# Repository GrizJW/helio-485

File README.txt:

Helio-485 Rev A — KiCad layout

Open helio-485.kicad_pcb. KiCad 10 (file version 20260206).

Board: 140 x 218 mm, 2 layer, 1.6 mm, 2 oz. No cell holders.
J5 is the 2S pouch (PACK−, PACK+). J6 is the balance lead (PACK−, midpoint, PACK+). Charge current is
set to 2 A, which is the TP5100 limit. U10 is an LM393 low-voltage
disconnect: it forces the 12 V boost off below 6.4 V on the pack.
J7 is the Ethernet jack. U11 is a W5500. The C5 has no MAC.

What is already done
- Official KiCad footprints for the holders, USB-C (HRO TYPE-C-31-M-12),
  Phoenix 5.08 mm terminals, SOT-23, SOT-23-6, SOIC-8, QFN-16, TO-252,
  TO-92, and the passives.
- ESP32-C5-WROOM-1 land from the Espressif pattern: 1.27 mm pitch,
  1.5 x 0.9 mm pads, row centers at ±8.0 mm, pad column span 16.51 mm,
  antenna at +Y. Pin 1 is the antenna-end pad on the left, marked with a dot.
- TPS61088 RHL0020A land from TI drawing 4219071. Pin 1 is the bottom-left
  pad. The exposed pad is pin 21 (PGND).
- Nets on every placed pad.
- J5 and J6 are the pack. PACK− is a 2 mm track into the sense resistor.
  PACK+ is a 2 mm track into F1. The midpoint is on J6 pin 2.
- Back copper is a GND zone. Press B to fill it.
- Antenna keepout is a rule area on both layers at the top-right. No copper.

What you still route
Everything else is a ratsnest. Do that in pcbnew, then run DRC.
Do not run Update PCB from Schematic. There is no schematic in this
project; the nets live on the board.

Check before you fab
- S-8252 pin numbers are the SOT-23-6 table: 1 DO, 2 CO, 3 VM, 4 VC,
  5 VDD, 6 VSS. VDD is the top of the stack.
- TP5100 pin numbers follow the datasheet grouping used on the rev A
  sheet (VIN on 1/4/5/16, LX on 2/3, BAT on 9). Confirm against the reel.
- AO3401A is G/S/D = pins 1/2/3. AOD510 is G/D/S = 1/2/3, tab is drain.
- USB-C (J4, HRO TYPE-C-31-M-12) is on the left edge, plug facing out.
  D+ / D− go through 22 Ω (Rdp, Rdm) to module pins 14 and 13
  (GPIO14 USB D+, GPIO13 USB D−). CC1 and CC2 are 5.1 kΩ to GND.
  D3 (B5819W, SOD-123 pin 1 = cathode) ORs VBUS onto VSYS so the
  3.3 V buck runs from the laptop when the pack is out. USB does not
  charge the cells. Full-speed only; the pair is not 90 Ω.
- USB-C programs the ESP32. J2 is the GEM2 supply: pin 1 yellow, pin 2 purple.
  J3 is RS-485 Modbus. Pin 1 is A (GEM2 pink), pin 2 is B (GEM2 green),
  pin 3 is ground. U6 is a THVD1400. GPIO5 drives D, GPIO4 reads R,
  GPIO6 is DE and /RE tied together. Ra and Rb are 10 ohm between the
  chip and the bus. D2 is an SM712 in SOT-23. Pins 1 and 2 are the
  same 12 V line clamps; this layout uses pin 1 as B and pin 2 as A so
  the two traces do not cross. Pin 3 is ground, with a via into the
  ground plane. SJ1 ships open, so the 120 ohm is not across the pair
  unless this node is an end of the cable.
  The meter wants external power for Modbus. That power is J2.
- Panel on J1: 30 W, Vmp about 16 V, Voc at or below 17 V. A normal
  12 V panel with Voc near 21 V will kill the TP5100. 2 A fills a
  10 Ah pack in about 6 hours of sun, not 4. That is the chip limit.
- U10 trips at 6.4 V on the pack and holds the 12 V rail off until
  the pack is about 0.3 V higher. GPIO23 cannot override it.
- Ethernet is SPI, not RMII. GPIO0 low enables Q5. Confirm the
  HR911105A land against the jack you buy before Gerbers.

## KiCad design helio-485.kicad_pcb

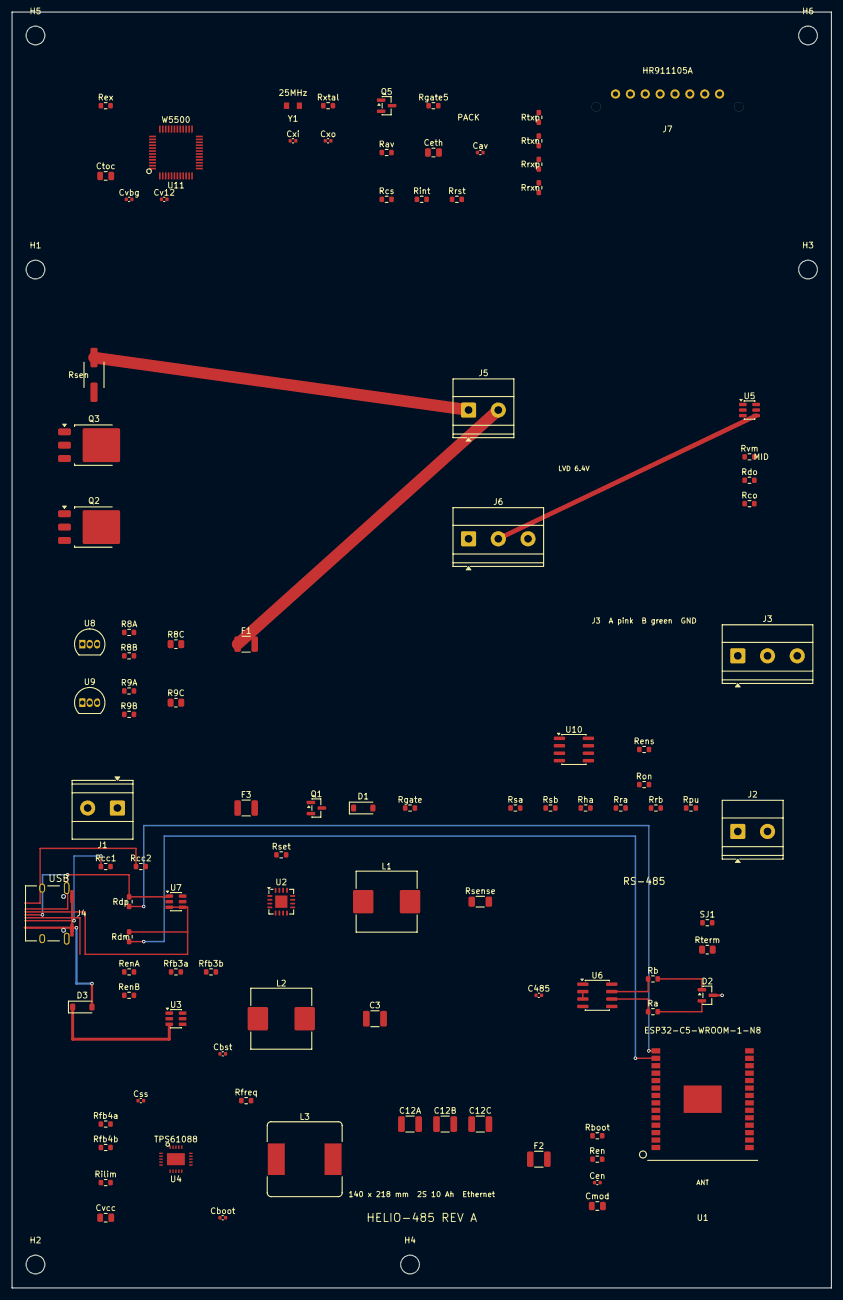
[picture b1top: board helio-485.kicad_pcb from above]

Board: 2 copper layers, 140.0 x 218.0 mm, 106 parts (0 on the bottom side), 80 nets.

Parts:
C3, C12A, C12B, C12C: 22uF; C_1210_3225Metric
C485: 100n; C_0402_1005Metric
Cav: 100n; C_0402_1005Metric
Cboot: 100n; C_0402_1005Metric
Cbst: 100n; C_0402_1005Metric
Cen: 1uF; C_0402_1005Metric
Ceth: 10uF; C_0805_2012Metric
Cmod: 10uF; C_0805_2012Metric
Css: 47n; C_0402_1005Metric
Ctoc: 4.7u; C_0805_2012Metric
Cv12: 10n; C_0402_1005Metric
Cvbg: 10n; C_0402_1005Metric
Cvcc: 1uF; C_0805_2012Metric
Cxi: 18p; C_0402_1005Metric
Cxo: 18p; C_0402_1005Metric
D1: BZT52C10; D_SOD-123
D2: SM712; SOT-23
D3: B5819W; D_SOD-123
F1: PTC-6A; R_1210_3225Metric
F2: PTC-2.5A; R_1210_3225Metric
F3: PTC-2A; R_1210_3225Metric
H1, H2, H3, H4, H5, H6: M3; MountingHole_3.2mm_M3
J1: PV; TerminalBlock_Phoenix_MKDS-1,5-2-5.08_1x02_P5.08mm_Horizont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
J2: 12V; TerminalBlock_Phoenix_MKDS-1,5-2-5.08_1x02_P5.08mm_Horizont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
J3: Modbus; TerminalBlock_Phoenix_MKDS-1,5-3-5.08_1x03_P5.08mm_Horizont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
J4: USB-C; USB_C_Receptacle_HRO_TYPE-C-31-M-12
J5: PACK; TerminalBlock_Phoenix_MKDS-1,5-2-5.08_1x02_P5.08mm_Horizont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
J6: BAL; TerminalBlock_Phoenix_MKDS-1,5-3-5.08_1x03_P5.08mm_Horizont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
J7: HR911105A; RJ45-Magjack
L1: 22uH; L_Wuerth_HCI-1040
L2: 4.7uH; L_Wuerth_HCI-1040
L3: 2.2uH; L_Bourns_SRR1260
Q1, Q5: AO3401A; SOT-23
Q2, Q3: AOD510; TO-252-3_TabPin2
R8A, R9A: 6.81k; R_0603_1608Metric
R8B, R9B: 10.0k; R_0603_1608Metric
R8C, R9C: 47; R_0805_2012Metric
Ra: 10; R_0603_1608Metric
Rav: 3.3; R_0603_1608Metric
Rb: 10; R_0603_1608Metric
Rboot: 10k; R_0603_1608Metric
Rcc1, Rcc2: 5.1k; R_0603_1608Metric
Rco: 100; R_0603_1608Metric
Rcs: 4.7k; R_0603_1608Metric
Rdm: 22; R_0603_1608Metric
Rdo: 100; R_0603_1608Metric
Rdp: 22; R_0603_1608Metric
Ren: 10k; R_0603_1608Metric
RenA: 100k; R_0603_1608Metric
RenB: 150k; R_0603_1608Metric
Rens: 10k; R_0603_1608Metric
Rex: 12.4k; R_0603_1608Metric
Rfb3a: 33.0k; R_0603_1608Metric
Rfb3b: 10.0k; R_0603_1608Metric
Rfb4a: 422k; R_0603_1608Metric
Rfb4b: 47.0k; R_0603_1608Metric
Rfreq: 255k; R_0603_1608Metric
Rgate, Rgate5: 100k; R_0603_1608Metric
Rha: 470k; R_0603_1608Metric
Rilim: 140k; R_0603_1608Metric
Rint: 4.7k; R_0603_1608Metric
Ron: 1k; R_0603_1608Metric
Rpu: 100k; R_0603_1608Metric
Rra: 17.4k; R_0603_1608Metric
Rrb: 10.0k; R_0603_1608Metric
Rrst: 4.7k; R_0603_1608Metric
Rrxn: 49.9; R_0603_1608Metric
Rrxp: 49.9; R_0603_1608Metric
Rsa: 43.2k; R_0603_1608Metric
Rsb: 10.0k; R_0603_1608Metric
Rsen: 0.010; R_2512_6332Metric
Rsense: 0.050; R_1206_3216Metric
Rset: 0; R_0603_1608Metric
Rterm: 120; R_0805_2012Metric
Rtxn: 49.9; R_0603_1608Metric
Rtxp: 49.9; R_0603_1608Metric
Rvm: 330; R_0603_1608Metric
Rxtal: 1M; R_0603_1608Metric
SJ1: OPEN; R_0603_1608Metric
U1: ESP32-C5-WROOM-1-N8; ESP32-C5-WROOM-1
U2: TP5100; QFN-16-1EP_4x4mm_P0.65mm_EP2.1x2.1mm
U3: TPS562208; SOT-23-6
U4: TPS61088; TPS61088-RHL
U5: S-8252; SOT-23-6
U6: THVD1400; SOIC-8_3.9x4.9mm_P1.27mm
U7: USBLC6-2; SOT-23-6
U8, U9: TL431A; TO-92_Inline
U10: LM393; SOIC-8_3.9x4.9mm_P1.27mm
U11: W5500
Y1: 25MHz; Crystal-3225

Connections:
12V_OUT: F2.2, J2.1
+3V3: C3.1, C485.1, Cmod.1, L2.2, Q5.2, Rboot.1, Ren.1, Rfb3a.1, Rgate5.2, Rpu.1, Rra.1, U1.2, U6.8, U10.8
+3V3_LDO: Cvcc.1, U4.1
+12V: C12A.1, C12B.1, C12C.1, F2.1, Rfb4a.1, U4.14, U4.15, U4.16
A: D2.2, J3.1, Ra.2, Rterm.1
AVDD: Cav.1, Rav.2, U11.4, U11.8, U11.11, U11.15, U11.17, U11.21
A_DRV: Ra.1, U6.6
B: D2.1, J3.2, Rb.2, SJ1.2
BOOT: Cboot.1, Rboot.2, U1.27, U4.8
BST3: Cbst.1, U3.6
B_DRV: Rb.1, U6.7
CATH1: R8A.1, R8C.2, U8.3
CATH2: R9A.1, R9C.2, U9.3
CC1: J4.A5, Rcc1.1
CC2: J4.B5, Rcc2.1
CO: Q2.1, Rco.1, Rco.2, U5.2
DO: Q3.1, Rdo.1, Rdo.2, U5.1
EN3: RenA.2, RenB.1, U3.5
EN12: Rens.2, Rha.1, Rpu.2, U4.2, U10.1
EN12_MCU: Rens.1, U1.21
EN_MCU: Cen.1, Ren.2, U1.3
ETH_3V3: Ceth.1, Q5.3, Rav.1, Rcs.1, Rint.1, Rrst.1, U11.28, U11.43, U11.44, U11.45
ETH_CS: Rcs.2, U1.11, U11.32
ETH_GATE: Q5.1, Rgate5.1, Ron.2
ETH_INT: Rint.2, U1.23, U11.36
ETH_MISO: U1.5, U11.34
ETH_MOSI: U1.12, U11.35
ETH_ON: Ron.1, U1.6
ETH_RST: Rrst.2, U1.26, U11.37
ETH_RXN: Rrxn.1, U11.5
ETH_RXN_J: J7.6, Rrxn.2
ETH_RXP: Rrxp.1, U11.6
ETH_RXP_J: J7.3, Rrxp.2
ETH_SCLK: U1.4, U11.33
ETH_TXN: Rtxn.1, U11.1
ETH_TXN_J: J7.2, Rtxn.2
ETH_TXP: Rtxp.1, U11.2
ETH_TXP_J: J7.1, Rtxp.2
EXRES: Rex.1, U11.10
FB3: Rfb3a.2, Rfb3b.1, U3.4
FB12: Rfb4a.2, Rfb4b.1, U4.17
FETSRC: Q2.3, Q3.3
FSW: Rfreq.1, U4.3
GATE: D1.1, Q1.1, Rgate.1
GND: C3.2, C12A.2, C12B.2, C12C.2, C485.2, Cav.2, Cen.2, Ceth.2, Cmod.2, Css.2, Ctoc.2, Cv12.2, Cvbg.2, Cvcc.2, Cxi.2, Cxo.2, D2.3, J1.2, J2.2, J3.3, J4.A1, J4.A12, J4.B1, J4.B12, J4.SH, J7.S1, J7.S2, Rcc1.2, Rcc2.2, RenB.2, Rex.2, Rfb3b.2, Rfb4b.2, Rgate.2, Rilim.2, Rrb.2, Rsb.2, U1.1, U1.28, U1.29, U2.7, U2.17, U3.1, U4.11, U4.12, U4.13, U4.20, U4.21, U6.5, U7.2, U10.4, U10.5, U10.6, U10.7, U11.3, U11.9, U11.14, U11.16, U11.19, U11.29, U11.48
ILIM: Rilim.1, U4.19
LVD_REF: Rra.2, Rrb.1, U10.2
LVD_SNS: Rha.2, Rsa.2, Rsb.1, U10.3
LX: L1.1, U2.2, U2.3
MID: J6.2, R8C.1, R9B.2, U5.4, U9.2
PACK+: F1.1, J5.2, J6.3, R9C.1, Rsense.2, U2.9, U5.5
PACK-: J5.1, J6.1, R8B.2, Rsen.1, U5.6, U8.2
PACKN_OUT: Q2.2, Rvm.2
PV: F3.1, J1.1
PVF: F3.2, Q1.3
REF1: R8A.2, R8B.1, U8.1
REF2: R9A.2, R9B.1, U9.1
RS485_DE: U1.8, U6.2, U6.3
RS485_RX: U1.17, U6.1
RS485_TX: U1.16, U6.4
SENSE: Q3.2, Rsen.2
SS: Css.1, U4.10
SW3: Cbst.2, L2.1, U3.2
SW4: Cboot.2, L3.2, Rfreq.2, U4.4, U4.5, U4.6, U4.7
TERM: Rterm.2, SJ1.1
TOCAP: Ctoc.1, U11.20
USB_DM: Rdm.2, U1.13
USB_DM_C: J4.A7, J4.B7, Rdm.1, U7.3, U7.4
USB_DP: Rdp.2, U1.14
USB_DP_C: J4.A6, J4.B6, Rdp.1, U7.1, U7.6
USB_VBUS: D3.2, J4.A4, J4.A9, J4.B4, J4.B9, U7.5
V12O: Cv12.1, U11.22
VBG: Cvbg.1, U11.18
VIN_CHG: D1.2, Q1.2, U2.1, U2.4, U2.5, U2.16
VM: Rvm.1, U5.3
VREG: Rset.1, Rset.2, U2.10, U2.13
VS: L1.2, Rsense.1, U2.8
VSYS: D3.1, F1.2, L3.1, RenA.1, Rsa.1, U3.3, U4.9
XTAL_XI: Cxi.1, Rxtal.1, U11.30, Y1.1
XTAL_XO: Cxo.1, Rxtal.2, U11.31, Y1.2
